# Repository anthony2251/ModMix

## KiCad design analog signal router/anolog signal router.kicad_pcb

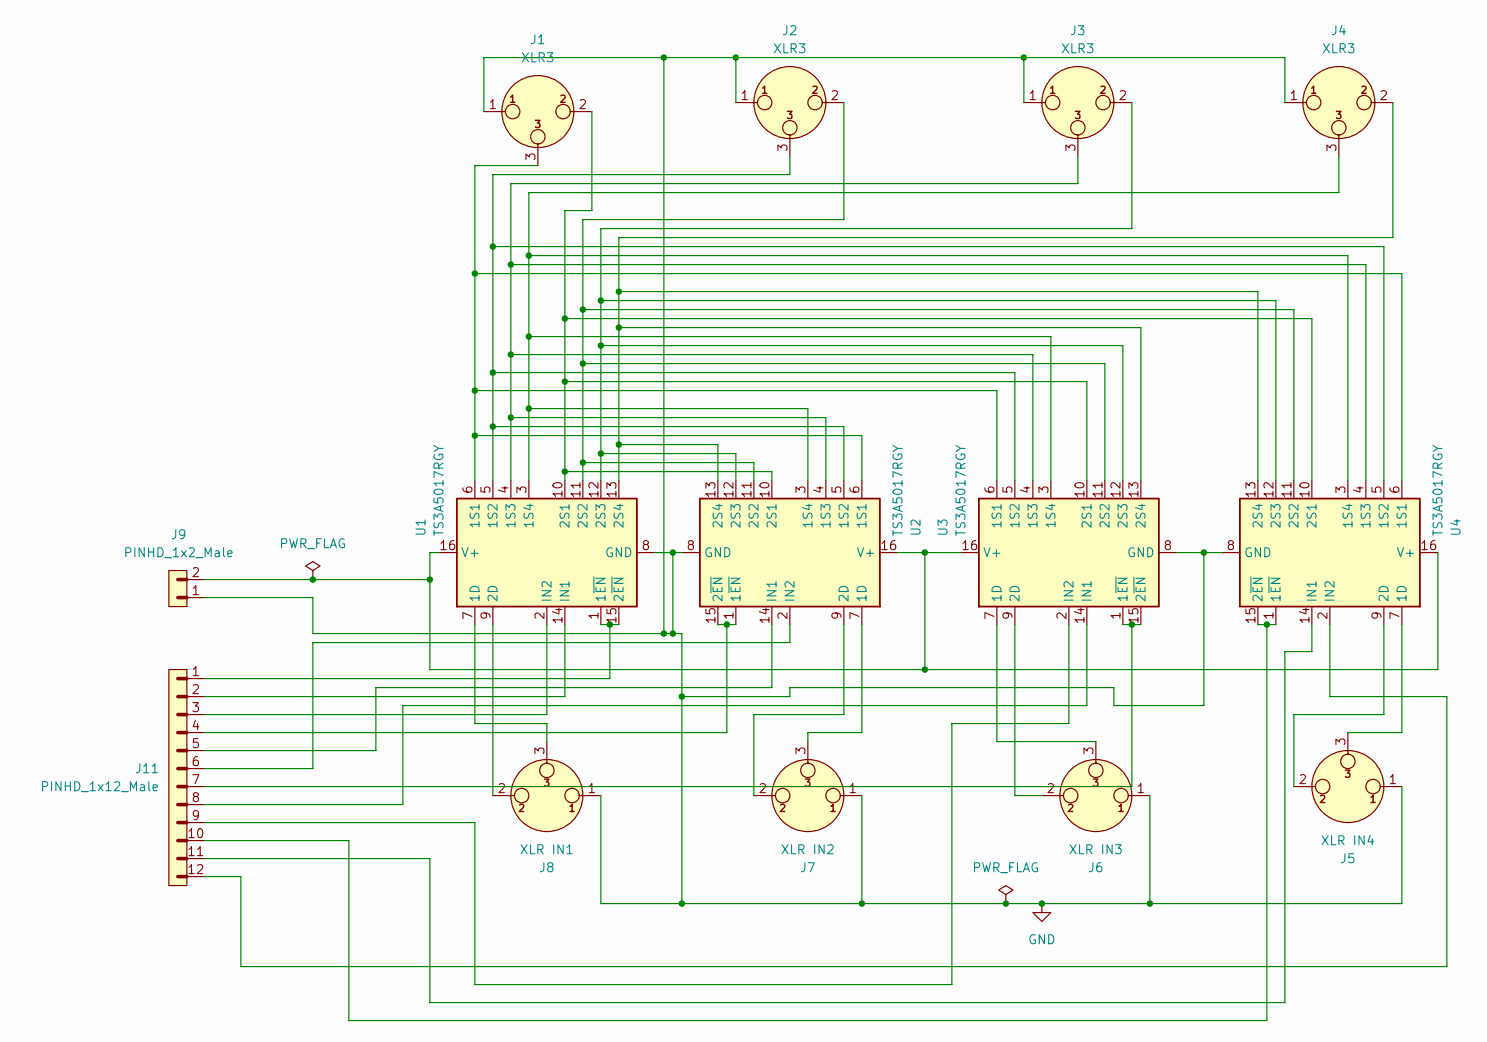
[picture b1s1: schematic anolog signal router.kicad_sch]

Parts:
J1, J2, J3, J4: XLR3; Jack_XLR_Neutrik_NC3MAAH-1_Horizontal
J5: XLR IN4; Jack_XLR_Neutrik_NC3FAH1-DA_Horizontal
J6: XLR IN3; Jack_XLR_Neutrik_NC3FAH1-DA_Horizontal
J7: XLR IN2; Jack_XLR_Neutrik_NC3FAH1-DA_Horizontal
J8: XLR IN1; Jack_XLR_Neutrik_NC3FAH1-DA_Horizontal
J9: PINHD_1x2_Male; PinHeader_1x02_P2.54mm_Vertical
J11: PINHD_1x12_Male; PinHeader_1x12_P2.54mm_Vertical
U1, U2, U3, U4: TS3A5017RGY; Texas_RGY_R-PVQFN-N16_EP2.05x2.55mm

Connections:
GND: J1.1, J2.1, J3.1, J4.1, J5.1, J6.1, J7.1, J8.1, J9.1, U1.8 (GND), U1.17 (GND), U2.8 (GND), U2.17 (GND), U3.8 (GND), U3.17 (GND), U4.8 (GND), U4.17 (GND)
unnamed: J8.3, U1.7 (1D)
unnamed: J1.3, U1.6 (1S1), U2.6 (1S1), U3.6 (1S1), U4.6 (1S1)
unnamed: J2.3, U1.5 (1S2), U2.5 (1S2), U3.5 (1S2), U4.5 (1S2)
unnamed: J3.3, U1.4 (1S3), U2.4 (1S3), U3.4 (1S3), U4.4 (1S3)
unnamed: J4.3, U1.3 (1S4), U2.3 (1S4), U3.3 (1S4), U4.3 (1S4)
unnamed: J11.1, U1.1 (1~EN), U1.15 (2~EN)
unnamed: J8.2, U1.9 (2D)
unnamed: J1.2, U1.10 (2S1), U2.10 (2S1), U3.10 (2S1), U4.10 (2S1)
unnamed: J2.2, U1.11 (2S2), U2.11 (2S2), U3.11 (2S2), U4.11 (2S2)
unnamed: J3.2, U1.12 (2S3), U2.12 (2S3), U3.12 (2S3), U4.12 (2S3)
unnamed: J4.2, U1.13 (2S4), U2.13 (2S4), U3.13 (2S4), U4.13 (2S4)
unnamed: J11.2, U1.14 (IN1)
unnamed: J11.3, U1.2 (IN2)
unnamed: J9.2, U1.16 (V+), U2.16 (V+), U3.16 (V+), U4.16 (V+)
unnamed: J7.3, U2.7 (1D)
unnamed: J11.4, U2.1 (1~EN), U2.15 (2~EN)
unnamed: J7.2, U2.9 (2D)
unnamed: J11.5, U2.14 (IN1)
unnamed: J11.6, U2.2 (IN2)
unnamed: J6.3, U3.7 (1D)
unnamed: J11.7, U3.1 (1~EN), U3.15 (2~EN)
unnamed: J6.2, U3.9 (2D)
unnamed: J11.8, U3.14 (IN1)
unnamed: J11.9, U3.2 (IN2)
unnamed: J5.3, U4.7 (1D)
unnamed: J11.10, U4.1 (1~EN), U4.15 (2~EN)
unnamed: J5.2, U4.9 (2D)
unnamed: J11.11, U4.14 (IN1)
unnamed: J11.12, U4.2 (IN2)

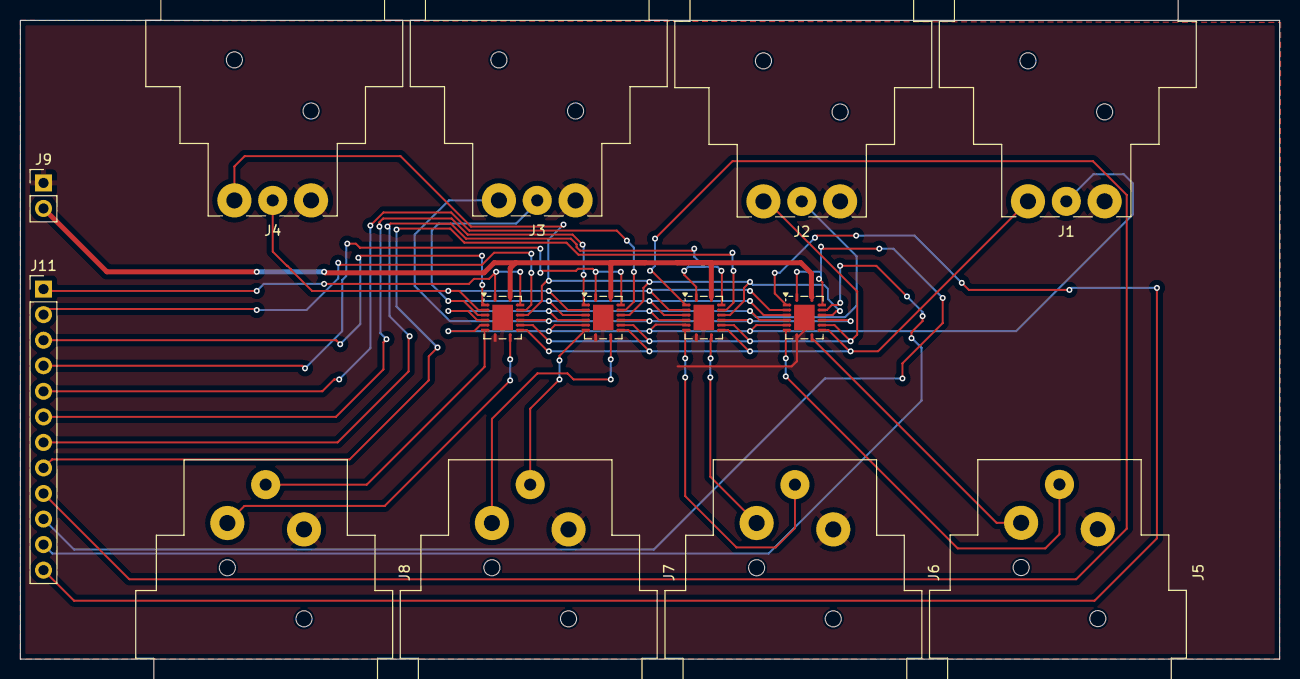
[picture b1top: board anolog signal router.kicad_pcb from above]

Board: 2 copper layers, 125.2 x 63.5 mm, 14 parts (0 on the bottom side), 30 nets.

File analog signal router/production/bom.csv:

Designator,Footprint,Quantity,Value,LCSC Part #
"J1, J2, J3, J4",Jack_XLR_Neutrik_NC3MAAH-1_Horizontal,4,XLR3,
J11,PinHeader_1x12_P2.54mm_Vertical,1,PINHD_1x12_Male,
J5,Jack_XLR_Neutrik_NC3FAH1-DA_Horizontal,1,XLR IN4,
J6,Jack_XLR_Neutrik_NC3FAH1-DA_Horizontal,1,XLR IN3,
J7,Jack_XLR_Neutrik_NC3FAH1-DA_Horizontal,1,XLR IN2,
J8,Jack_XLR_Neutrik_NC3FAH1-DA_Horizontal,1,XLR IN1,
J9,PinHeader_1x02_P2.54mm_Vertical,1,PINHD_1x2_Male,
"U1, U2, U3, U4",Texas_RGY_R-PVQFN-N16_EP2.05x2.55mm,4,TS3A5017RGY,

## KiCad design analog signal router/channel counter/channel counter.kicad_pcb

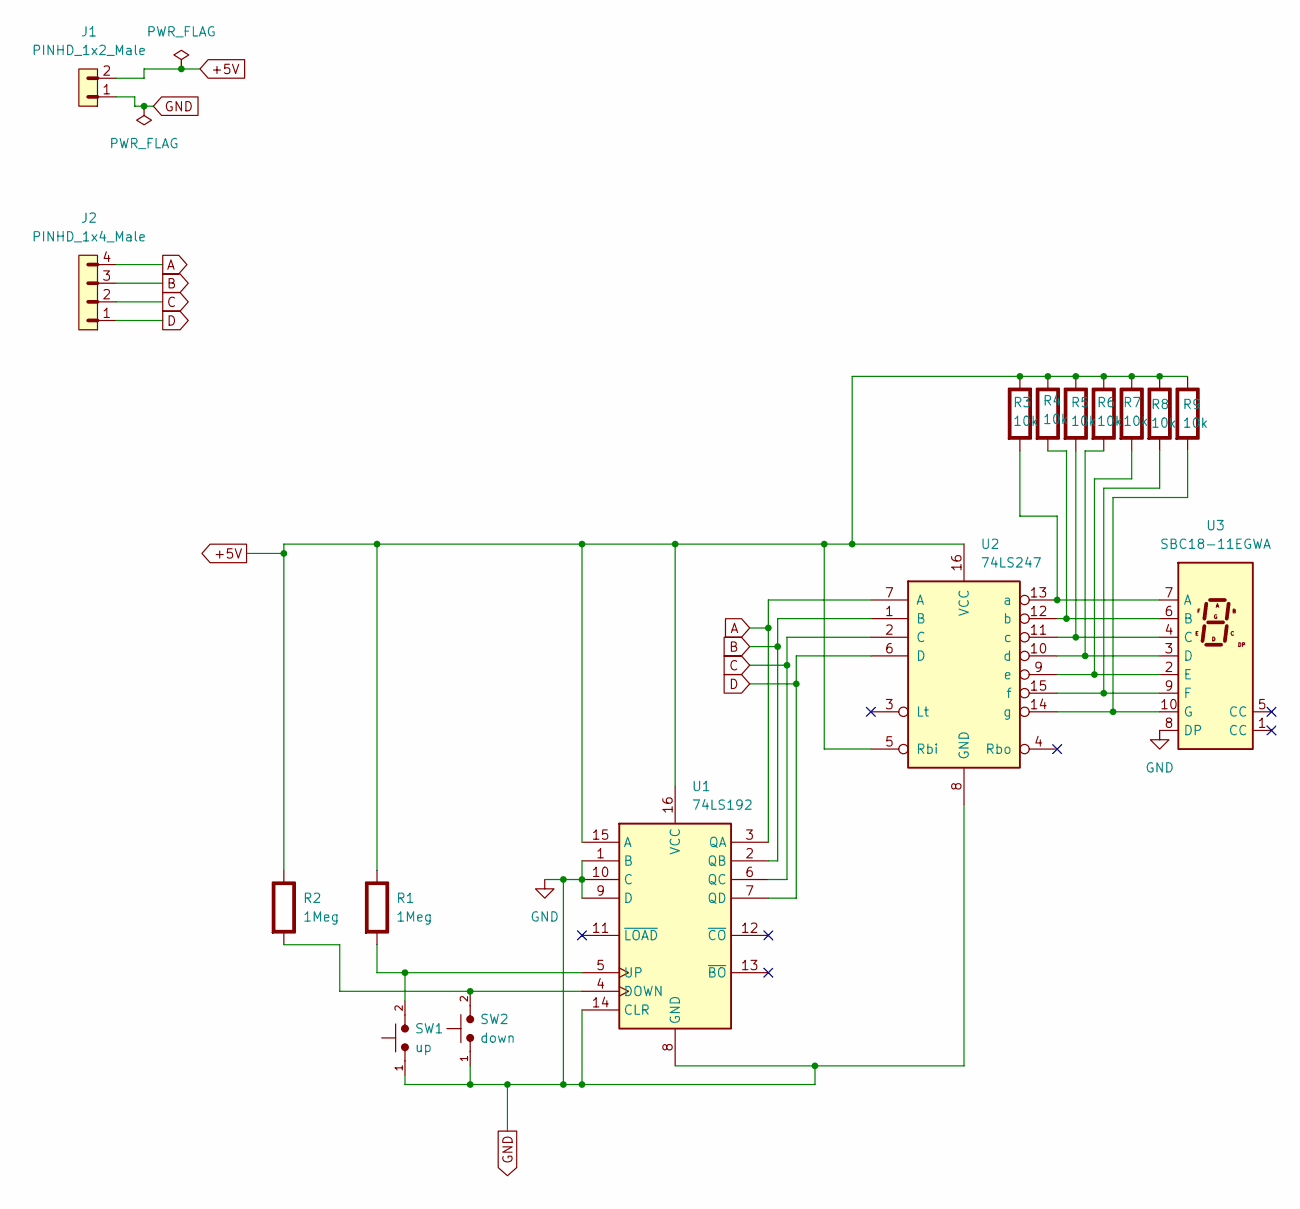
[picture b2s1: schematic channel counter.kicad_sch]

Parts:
J1: PINHD_1x2_Male; PinHeader_1x02_P2.54mm_Vertical
J2: PINHD_1x4_Male; PinHeader_1x04_P2.54mm_Vertical
R1, R2: 1Meg; R_Axial_DIN0204_L3.6mm_D1.6mm_P7.62mm_Horizontal; Rating W
R3, R4, R5, R6, R7, R8, R9: 10k; R_Axial_DIN0204_L3.6mm_D1.6mm_P7.62mm_Horizontal; Rating W
SW1: up; SW_PUSH_6mm
SW2: down; SW_PUSH_6mm
U1: 74LS192; DIP-16_W7.62mm_IC_Socket
U2: 74LS247; DIP-16_W7.62mm_IC_Socket
U3: SBC18-11EGWA; SBC18-11SURKCGKWA

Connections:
+5V: J1.2, R1.1 (+), R2.1 (+), R3.1 (+), R4.1 (+), R5.1 (+), R6.1 (+), R7.1 (+), R8.1 (+), R9.1 (+), U1.15 (A), U1.16 (VCC), U2.5 (Rbi), U2.16 (VCC)
A: J2.4, U1.3 (QA), U2.7 (A)
B: J2.3, U1.2 (QB), U2.1 (B)
C: J2.2, U1.6 (QC), U2.2 (C)
D: J2.1, U1.7 (QD), U2.6 (D)
GND: J1.1, SW1.1, SW2.1, U1.1 (B), U1.8 (GND), U1.9 (D), U1.10 (C), U1.14 (CLR), U2.8 (GND), U3.8 (DP)
unnamed: R1.2 (-), SW1.2, U1.5 (UP)
unnamed: R2.2 (-), SW2.2, U1.4 (DOWN)
unnamed: R3.2 (-), U2.13 (a), U3.7 (A)
unnamed: R4.2 (-), U2.12 (b), U3.6 (B)
unnamed: R5.2 (-), U2.11 (c), U3.4 (C)
unnamed: R6.2 (-), U2.10 (d), U3.3 (D)
unnamed: R7.2 (-), U2.9 (e), U3.2 (E)
unnamed: R8.2 (-), U2.15 (f), U3.9 (F)
unnamed: R9.2 (-), U2.14 (g), U3.10 (G)

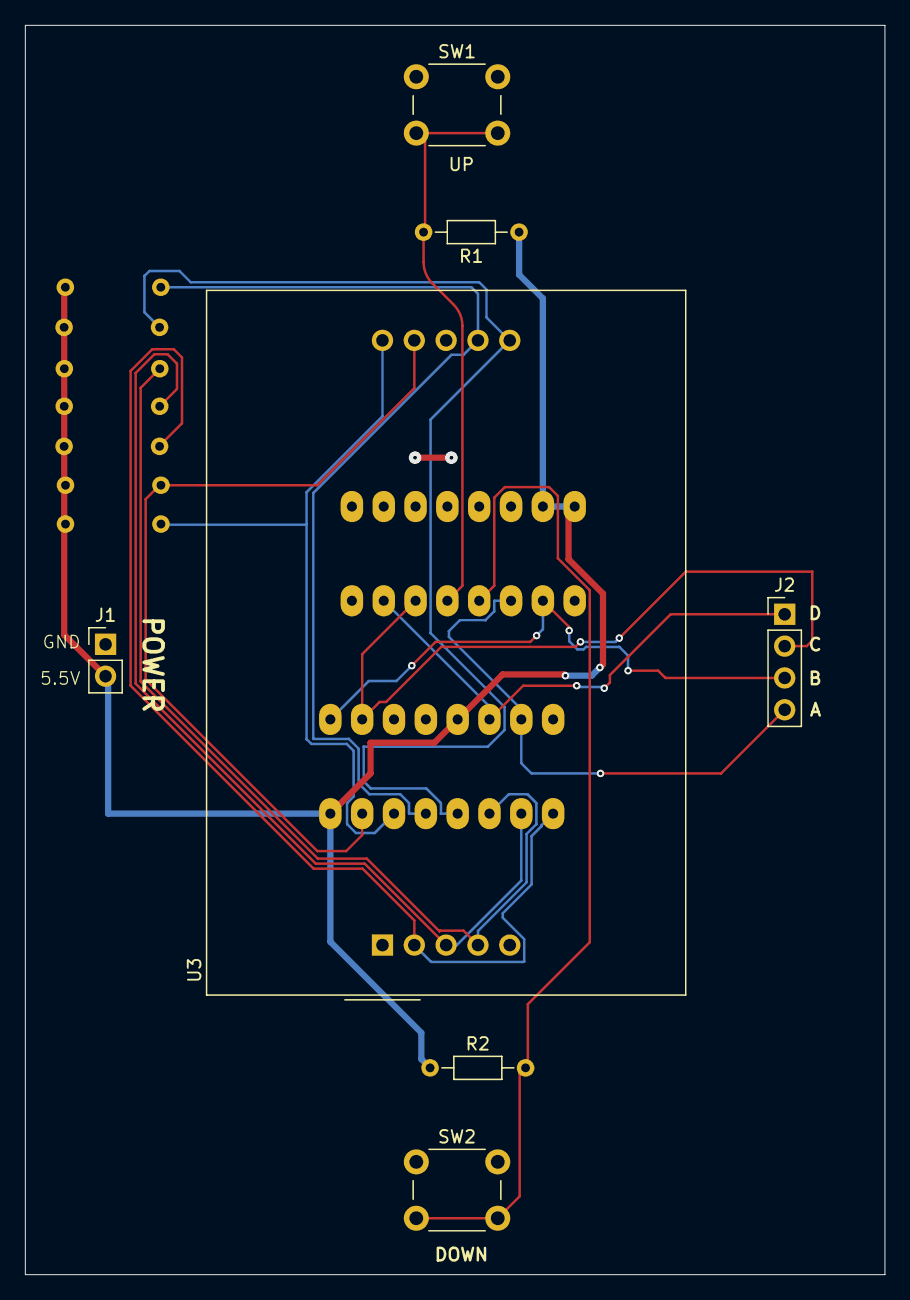
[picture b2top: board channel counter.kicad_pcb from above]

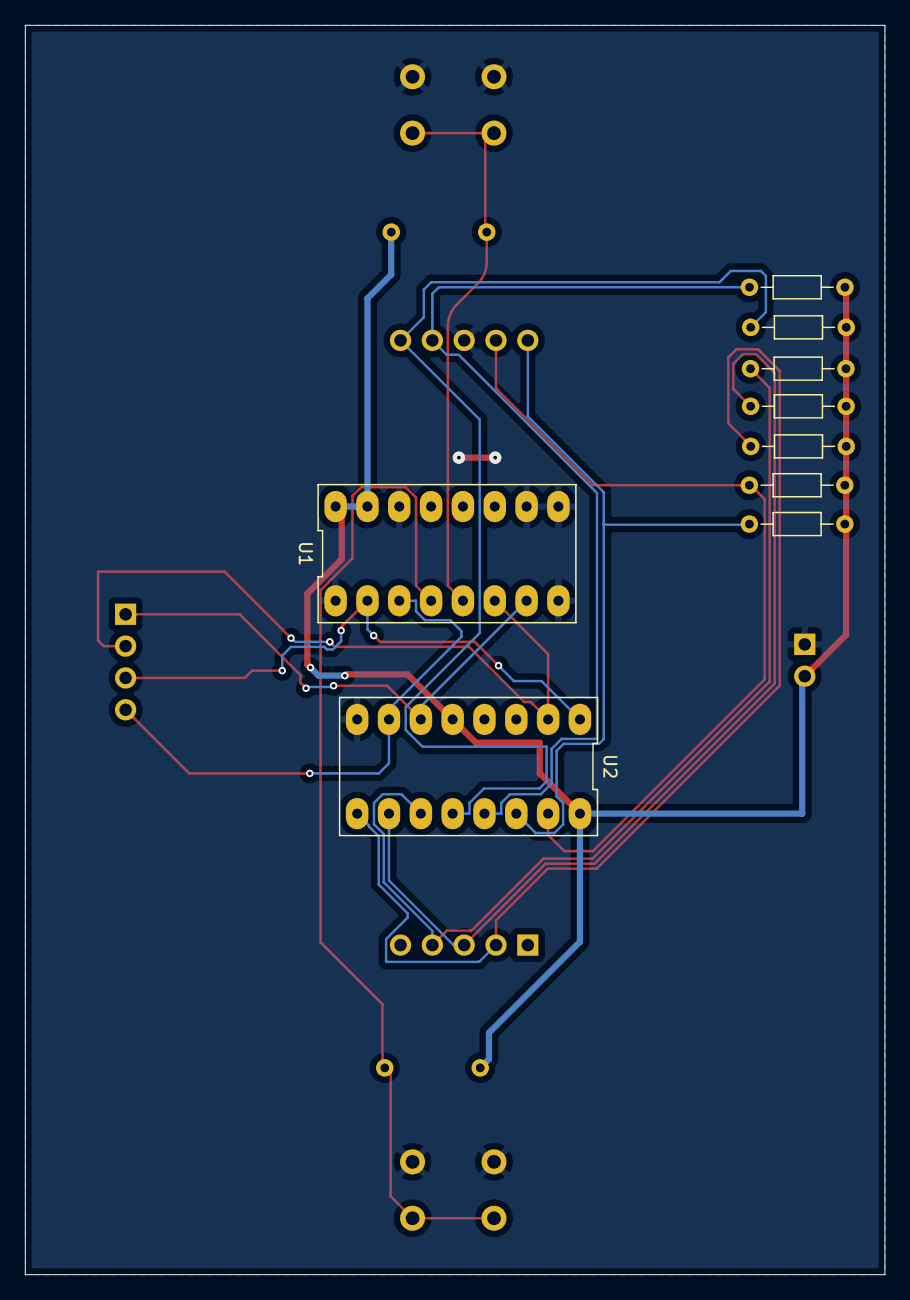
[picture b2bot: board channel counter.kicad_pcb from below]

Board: 2 copper layers, 68.6 x 99.7 mm, 16 parts (9 on the bottom side), 15 nets.

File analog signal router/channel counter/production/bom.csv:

Designator,Footprint,Quantity,Value,LCSC Part #
J1,PinHeader_1x02_P2.54mm_Vertical,1,PINHD_1x2_Male,
J2,PinHeader_1x04_P2.54mm_Vertical,1,PINHD_1x4_Male,
"R1, R2",R_Axial_DIN0204_L3.6mm_D1.6mm_P7.62mm_Horizontal,2,1Meg,
"R3, R4, R5, R6, R7, R8, R9",R_Axial_DIN0204_L3.6mm_D1.6mm_P7.62mm_Horizontal,7,10k,
SW1,SW_PUSH_6mm,1,up,
SW2,SW_PUSH_6mm,1,down,
U1,DIP-16_W7.62mm_IC_Socket,1,74LS192,
U2,DIP-16_W7.62mm_IC_Socket,1,74LS247,
U3,SBC18-11SURKCGKWA,1,SBC18-11EGWA,

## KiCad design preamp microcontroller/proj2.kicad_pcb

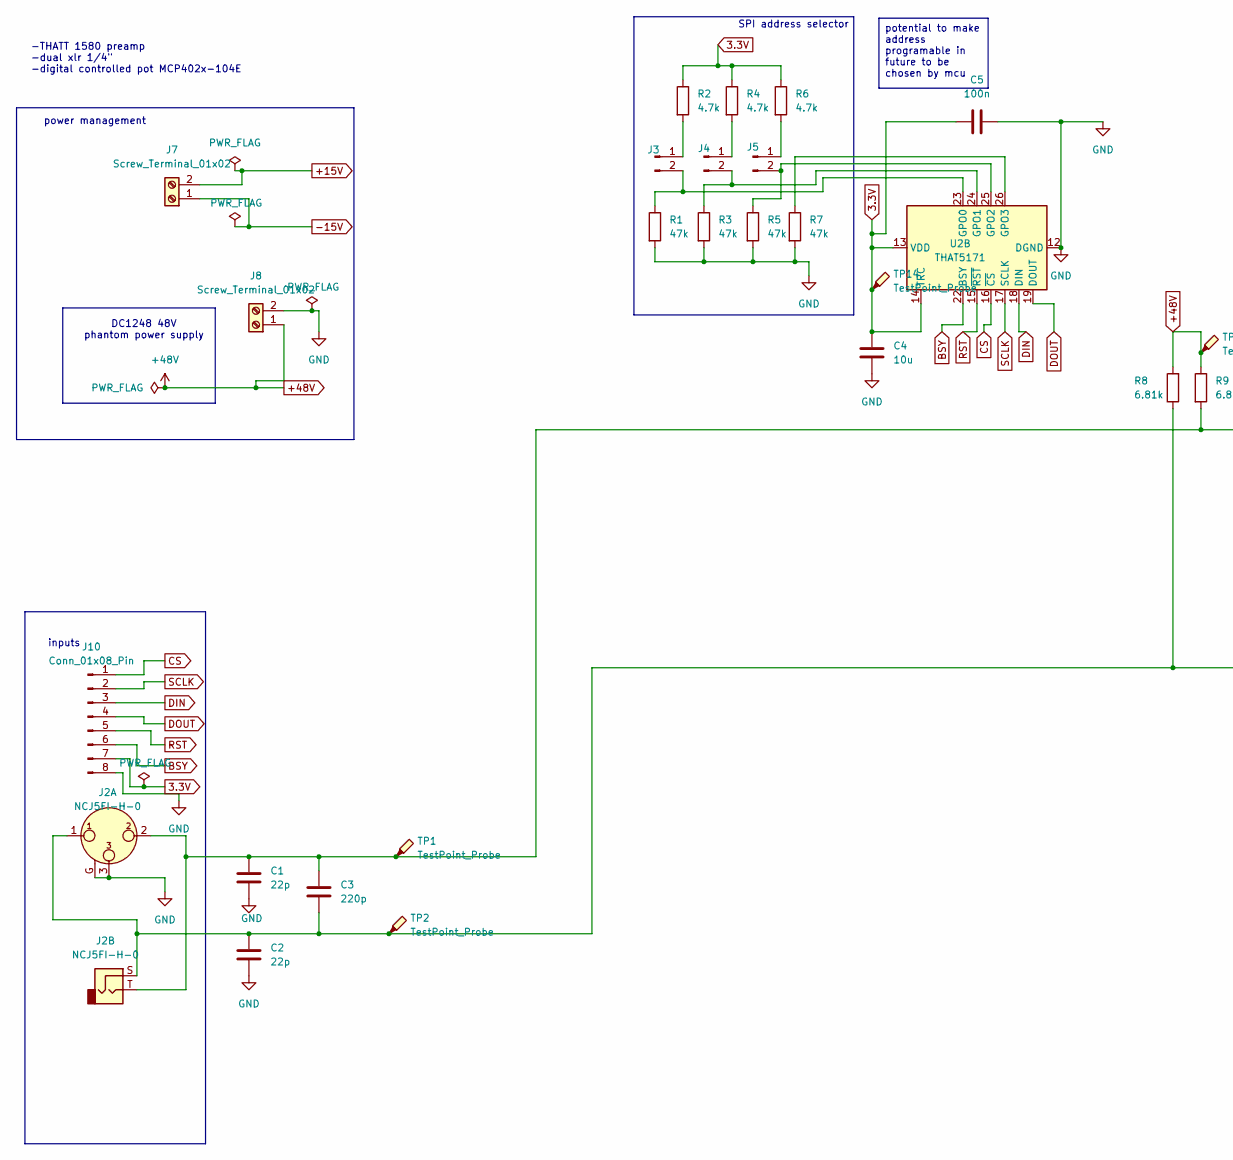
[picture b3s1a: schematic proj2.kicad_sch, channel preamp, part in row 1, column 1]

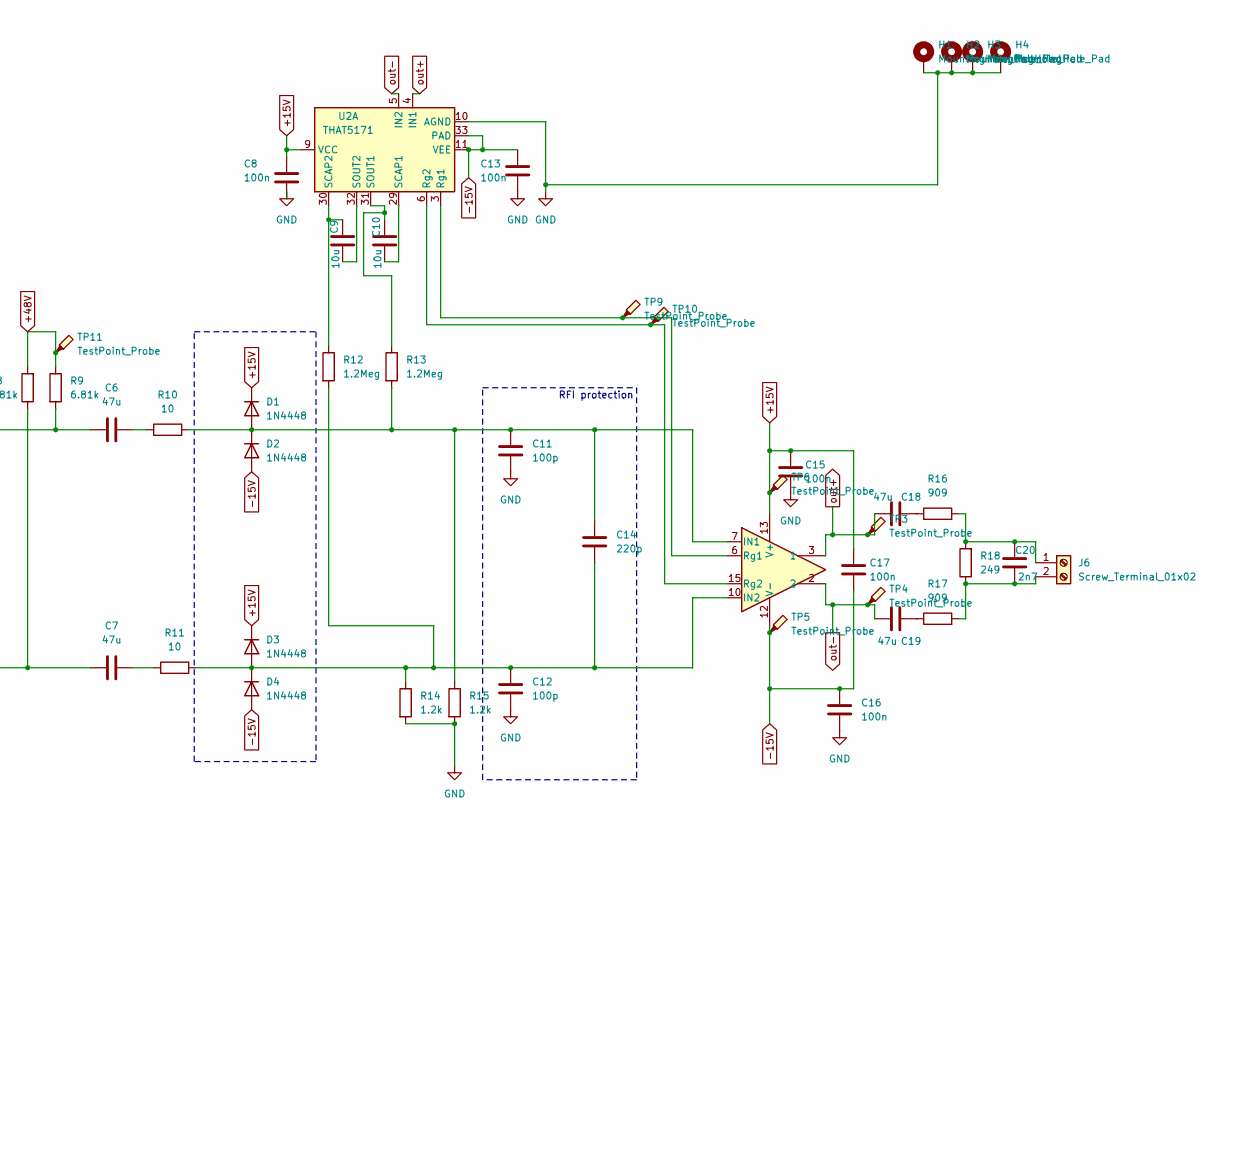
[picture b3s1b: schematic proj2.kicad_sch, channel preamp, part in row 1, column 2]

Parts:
C1, C2: 22p; C_Disc_D5.0mm_W2.5mm_P2.50mm
C3, C14: 220p; C_Disc_D5.0mm_W2.5mm_P5.00mm
C4, C9, C10: 10u; C_Disc_D5.0mm_W2.5mm_P2.50mm
C5, C8, C13, C15, C16, C17: 100n; C_Disc_D5.0mm_W2.5mm_P5.00mm
C6, C7: 47u; C_Disc_D5.0mm_W2.5mm_P5.00mm
C11, C12: 100p; C_Disc_D5.0mm_W2.5mm_P5.00mm
C18, C19: 47u; C_0201_0603Metric_Pad0.64x0.40mm_HandSolder
C20: 2n7; C_0201_0603Metric_Pad0.64x0.40mm_HandSolder
D1, D2, D3, D4: 1N4448; D_DO-35_SOD27_P7.62mm_Horizontal
H1, H2, H3, H4: MountingHole_Pad; MountingHole_2.2mm_M2_DIN965_Pad_TopBottom
J2: NCJ5FI-H-0; Jack_XLR-6.35mm_Neutrik_NCJ5FI-H-0_Horizontal
J3, J4, J5: Conn_01x02_Pin; PinHeader_1x02_P2.54mm_Vertical
J6, J7, J8: Screw_Terminal_01x02; TerminalBlock_RND_205-00001_1x02_P5.00mm_Horizontal
J10: Conn_01x08_Pin; PinSocket_1x08_P2.54mm_Vertical
R1, R3, R5, R7: 47k; R_Axial_DIN0207_L6.3mm_D2.5mm_P10.16mm_Horizontal
R2, R4, R6: 4.7k; R_Axial_DIN0207_L6.3mm_D2.5mm_P10.16mm_Horizontal
R8, R9: 6.81k; R_Axial_DIN0207_L6.3mm_D2.5mm_P10.16mm_Horizontal
R10, R11: 10; R_Axial_DIN0207_L6.3mm_D2.5mm_P10.16mm_Horizontal
R12, R13: 1.2Meg; R_Axial_DIN0207_L6.3mm_D2.5mm_P10.16mm_Horizontal
R14, R15: 1.2k; R_Axial_DIN0207_L6.3mm_D2.5mm_P10.16mm_Horizontal
R16, R17: 909; R_Axial_DIN0207_L6.3mm_D2.5mm_P10.16mm_Horizontal
R18: 249; R_Axial_DIN0207_L6.3mm_D2.5mm_P10.16mm_Horizontal
TP1, TP2, TP3, TP4, TP5, TP6, TP9, TP10, TP11, TP14: TestPoint_Probe; PinSocket_1x01_P2.54mm_Vertical
U2: THAT5171; QFN-32-1EP_7x7mm_P0.65mm_EP5.4x5.4mm
U3: THAT1580; QFN-16-1EP_4x4mm_P0.65mm_EP2.1x2.1mm_ThermalVias

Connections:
3.3V: C4.1, C5.1, J10.7, R2.1, R4.1, R6.1, TP14.1, U2.13 (VDD), U2.14 (TRC), U2.21 (VDD)
+15V: C8.1, C15.1, C17.1, D1.1 (K), D3.1 (K), J7.2, TP6.1, U2.9 (VCC), U3.13 (V+)
+48V: J8.1, R8.2, R9.1, TP11.1
-15V: C13.1, C16.1, C17.2, D2.2 (A), D4.2 (A), J7.1, TP5.1, U2.11 (VEE), U2.33 (PAD), U3.12 (V-), U3.17 (V-)
BSY: J10.6, U2.22 (BSY)
CS: J10.1, U2.16 (~CS)
DIN: J10.3, U2.18 (DIN)
DOUT: J10.4, U2.19 (DOUT)
GND: C1.2, C2.2, C4.2, C5.2, C8.2, C11.2, C12.2, C13.2, C15.2, C16.2, H1.1, H2.1, H3.1, H4.1, J2.3, J2.G, J8.2, J10.8, R1.2, R3.2, R5.2, R7.2, R14.2, R15.2, U2.10 (AGND), U2.12 (DGND), U2.20 (DGND), U2.28 (AGND)
unnamed: C1.1, C3.1, C6.2, J2.2, J2.T, R9.2, TP1.1
unnamed: C2.1, C3.2, C7.2, J2.1, J2.S, R8.1, TP2.1
unnamed: C6.1, R10.1
unnamed: C7.1, R11.1
unnamed: C18.2, R16.1
unnamed: C19.2, R17.1
unnamed: C11.1, C14.1, D1.2 (A), D2.1 (K), R10.2, R13.2, R15.1, U3.7 (IN1)
unnamed: C12.1, C14.2, D3.2 (A), D4.1 (K), R11.2, R12.2, R14.1, U3.10 (IN2)
unnamed: J3.1, R2.2
unnamed: J3.2, R1.1, U2.23 (GPO0)
unnamed: J4.1, R4.2
unnamed: J4.2, R3.1, U2.24 (GPO1)
unnamed: J5.1, R6.2
unnamed: J5.2, R5.1, U2.25 (GPO2)
unnamed: C20.1, J6.1, R16.2, R18.2
unnamed: C20.2, J6.2, R17.2, R18.1
unnamed: TP9.1, U2.3 (Rg1), U3.6 (Rg1)
unnamed: TP10.1, U2.6 (Rg2), U3.15 (Rg2)
unnamed: C10.2, U2.29 (SCAP1)
unnamed: C9.1, R12.1, U2.30 (SCAP2)
unnamed: C10.1, R13.1, U2.31 (SOUT1)
unnamed: C9.2, U2.32 (SOUT2)
unnamed: R7.1, U2.26 (GPO3)
RST: J10.5, U2.15 (~RST)
SCLK: J10.2, U2.17 (SCLK)
out+: C18.1, TP3.1, U2.4 (IN1), U3.3 (1)
out-: C19.1, TP4.1, U2.5 (IN2), U3.2

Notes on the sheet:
potential to make address programable in future to be chosen by mcu
RFI protection
-THATT 1580 preamp -dual xlr 1/4" -digital controlled pot MCP402x-104E
DC1248 48V phantom power supply
inputs
SPI address selector
power management

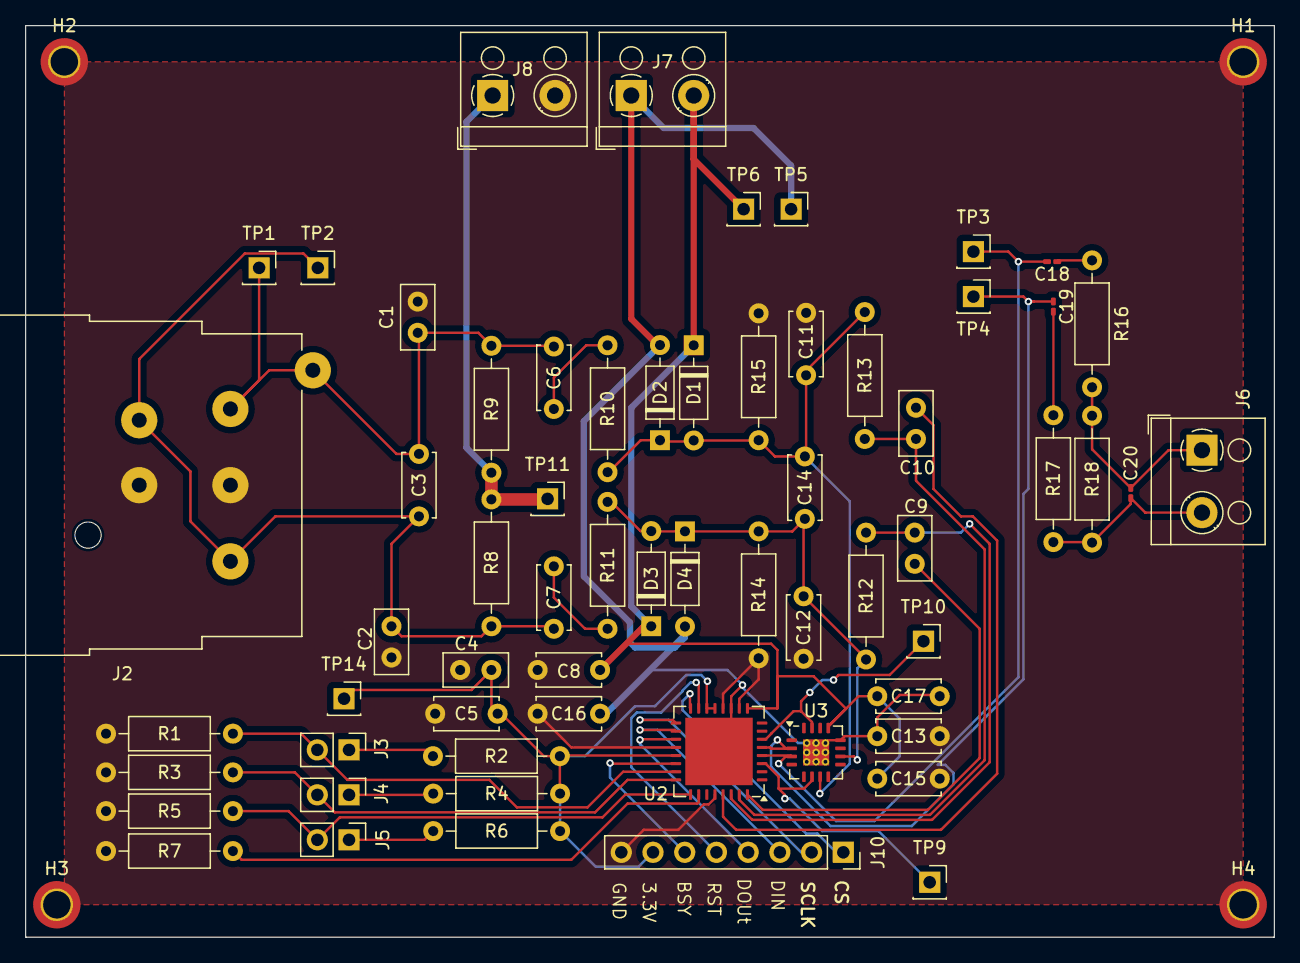
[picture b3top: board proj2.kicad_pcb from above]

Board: 2 copper layers, 100.0 x 73.0 mm, 66 parts (0 on the bottom side), 36 nets.

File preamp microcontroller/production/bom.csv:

Designator,Footprint,Quantity,Value,LCSC Part #
"C1, C2",0201,2,22p,
"C10, C4, C9",0201,3,10u,
"C11, C12",0201,2,100p,
"C13, C15, C16, C17, C5, C8",0201,6,100n,
"C14, C3",0201,2,220p,
"C18, C19, C6, C7",0201,4,47u,
C20,0201,1,2n7,
"D1, D2, D3, D4",D_DO-35_SOD27_P7.62mm_Horizontal,4,1N4448,
J10,PinHeader_1x08_P1.27mm_Vertical,1,Conn_01x08_Pin,
J2,Jack_XLR-6.35mm_Neutrik_NCJ5FI-H-0_Horizontal,1,NCJ5FI-H-0,
"J3, J4, J5",PinHeader_1x02_P2.54mm_Vertical,3,Conn_01x02_Pin,
"J6, J7, J8",TerminalBlock_RND_205-00001_1x02_P5.00mm_Horizontal,3,Screw_Terminal_01x02,
"R1, R3, R5, R7",0402,4,47k,
"R10, R11",0402,2,10,
"R12, R13",0402,2,1.2Meg,
"R14, R15",0402,2,1.2k,
"R16, R17",0402,2,909,
R18,0402,1,249,
"R2, R4, R6",0402,3,4.7k,
"R8, R9",0402,2,6.81k,
U2,QFN-32-1EP_7x7mm_P0.65mm_EP5.4x5.4mm,1,THAT5171,
U3,QFN-16-1EP_4x4mm_P0.65mm_EP2.1x2.1mm_ThermalVias,1,THAT1580,

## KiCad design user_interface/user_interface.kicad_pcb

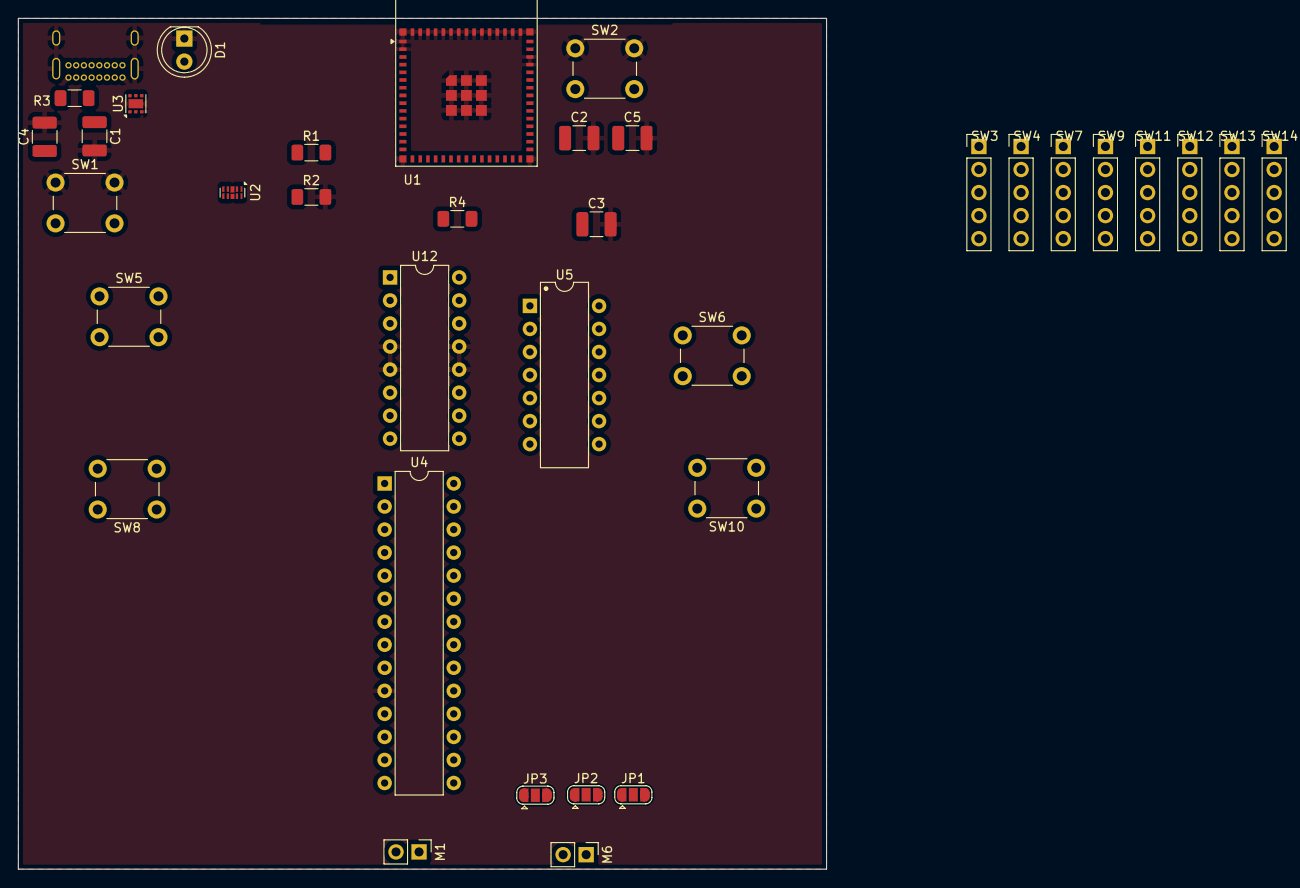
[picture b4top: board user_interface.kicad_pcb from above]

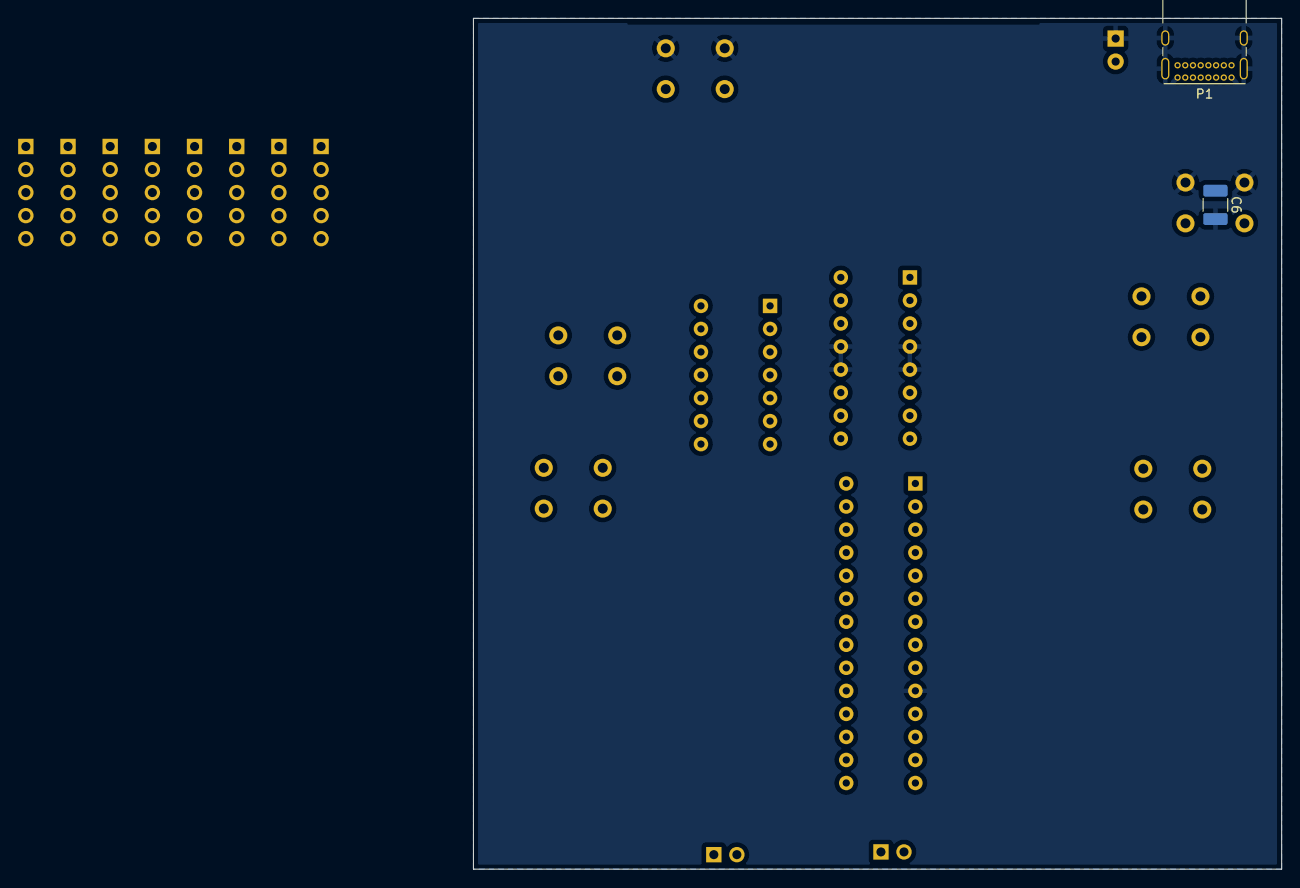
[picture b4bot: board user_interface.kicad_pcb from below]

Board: 4 copper layers, 89.1 x 93.8 mm, 37 parts (2 on the bottom side), 22 nets, no tracks yet.

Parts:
C1, C3, C4: 10uF; C_1210_3225Metric_Pad1.33x2.70mm_HandSolder
C2, C5, C6: 0.1uF; C_1210_3225Metric_Pad1.33x2.70mm_HandSolder
D1: LED; LED_D5.0mm
JP1: A2; SolderJumper-3_P1.3mm_Open_RoundedPad1.0x1.5mm
JP2: A1; SolderJumper-3_P1.3mm_Open_RoundedPad1.0x1.5mm
JP3: A0; SolderJumper-3_P1.3mm_Open_RoundedPad1.0x1.5mm
M1, M6: Fader1 motor; PinHeader_1x02_P2.54mm_Vertical
P1: USB_C_Plug_USB2.0; USB_C_Receptacle_GCT_USB4085
R1: 1M; R_1206_3216Metric_Pad1.30x1.75mm_HandSolder
R2: 200k; R_1206_3216Metric_Pad1.30x1.75mm_HandSolder
R3: 5.1k; R_1206_3216Metric_Pad1.30x1.75mm_HandSolder
R4: 10K; R_1206_3216Metric_Pad1.30x1.75mm_HandSolder
SW1, SW2: Push_Button; SW_PUSH_6mm
SW3, SW4, SW7, SW9, SW13, SW14: RotaryEncoder_Switch; PinHeader_1x05_P2.54mm_Vertical
SW5, SW6: Mute_Button; SW_PUSH_6mm
SW8, SW10: Sel_Button; SW_PUSH_6mm
SW11: RotaryEncoder_Switch CH2; PinHeader_1x05_P2.54mm_Vertical
SW12: RotaryEncoder_Switch_CH1; PinHeader_1x05_P2.54mm_Vertical
U1: ESP32-S3-MINI-1; ESP32-S2-MINI-1
U2: D3V3XA4B10LP; Diodes_UDFN-10_1.0x2.5mm_P0.5mm
U3: TLV75801PDRV; WSON-6-1EP_2x2mm_P0.65mm_EP1x1.6mm
U4: MCP23017_SP; DIP-28_W7.62mm
U5: 74LS04; DIP-14_W7.62mm
U12: L293D; DIP-16_W7.62mm

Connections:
3V3: C2.1 (+), C3.1 (+), C4.1 (+), R1.1 (+), R3.2 (-), R4.1 (+), U1.3 (3V3), U3.1 (OUT)
5VUSB: C1.1 (+), P1.A4 (VBUS), P1.A9 (VBUS), P1.B4 (VBUS), P1.B9 (VBUS), U2.4, U2.7 (NC), U3.4 (EN), U3.6 (IN), U12.8 (VCC2)
Fader direction: U5.1, U12.2 (1A), U12.10 (3A)
GND: C1.2 (-), C2.2 (-), C3.2 (-), C4.2 (-), C5.2 (-), C6.2 (-), D1.1, P1.A1 (GND), P1.A12 (GND), P1.B1 (GND), P1.B12 (GND), P1.S1 (SHIELD), R2.2 (-), SW1.1, SW2.1, U1.1 (GND), U1.2 (GND), U1.42 (GND), U1.43 (GND), U1.46 (GND), U1.47 (GND), U1.48 (GND), U1.49 (GND), U1.50 (GND), U1.51 (GND), U1.52 (GND), U1.53 (GND), U1.54 (GND), U1.55 (GND), U1.56 (GND), U1.57 (GND), U1.58 (GND), U1.59 (GND), U1.60 (GND), U1.61 (GND), U1.62 (GND), U1.63 (GND), U1.64 (GND), U1.65 (GND), U2.3 (VSS), U2.8 (VSS), U3.3 (GND), U3.7 (GND), U4.10 (VSS), U12.4 (GND), U12.5 (GND), U12.12 (GND), U12.13 (GND)
unnamed: C5.1 (+), R4.2 (-), SW1.2, U1.45 (EN)
unnamed: C6.1 (+), SW2.2, U1.4 (IO0)
unnamed: M1.1 (+), U12.3 (1Y)
unnamed: M1.2 (-), U12.6 (2Y)
unnamed: M6.1 (+), U12.11 (3Y)
unnamed: M6.2 (-), U12.14 (4Y)
unnamed: JP1.2 (C), U4.17 (A2)
unnamed: JP2.2 (C), U4.16 (A1)
unnamed: JP3.2 (C), U4.15 (A0)
unnamed: R1.2 (-), R2.1 (+), U3.2 (FB)
unnamed: D1.2, R3.1 (+)
unnamed: SW5.1, SW6.1
unnamed: U5.2, U12.7 (2A), U12.15 (4A)
SCL: U1.6 (IO2), U4.12 (SCK)
SDA: U1.7 (IO3), U4.13 (SDA)
USB_N: P1.A7 (D-), U1.23 (IO19), U2.1, U2.10 (NC)
USB_P: P1.A6 (D+), U1.24 (IO20), U2.2, U2.9 (NC)
int: U4.19 (INTB), U4.20 (INTA)

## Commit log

2025-06-27 Change folder name
